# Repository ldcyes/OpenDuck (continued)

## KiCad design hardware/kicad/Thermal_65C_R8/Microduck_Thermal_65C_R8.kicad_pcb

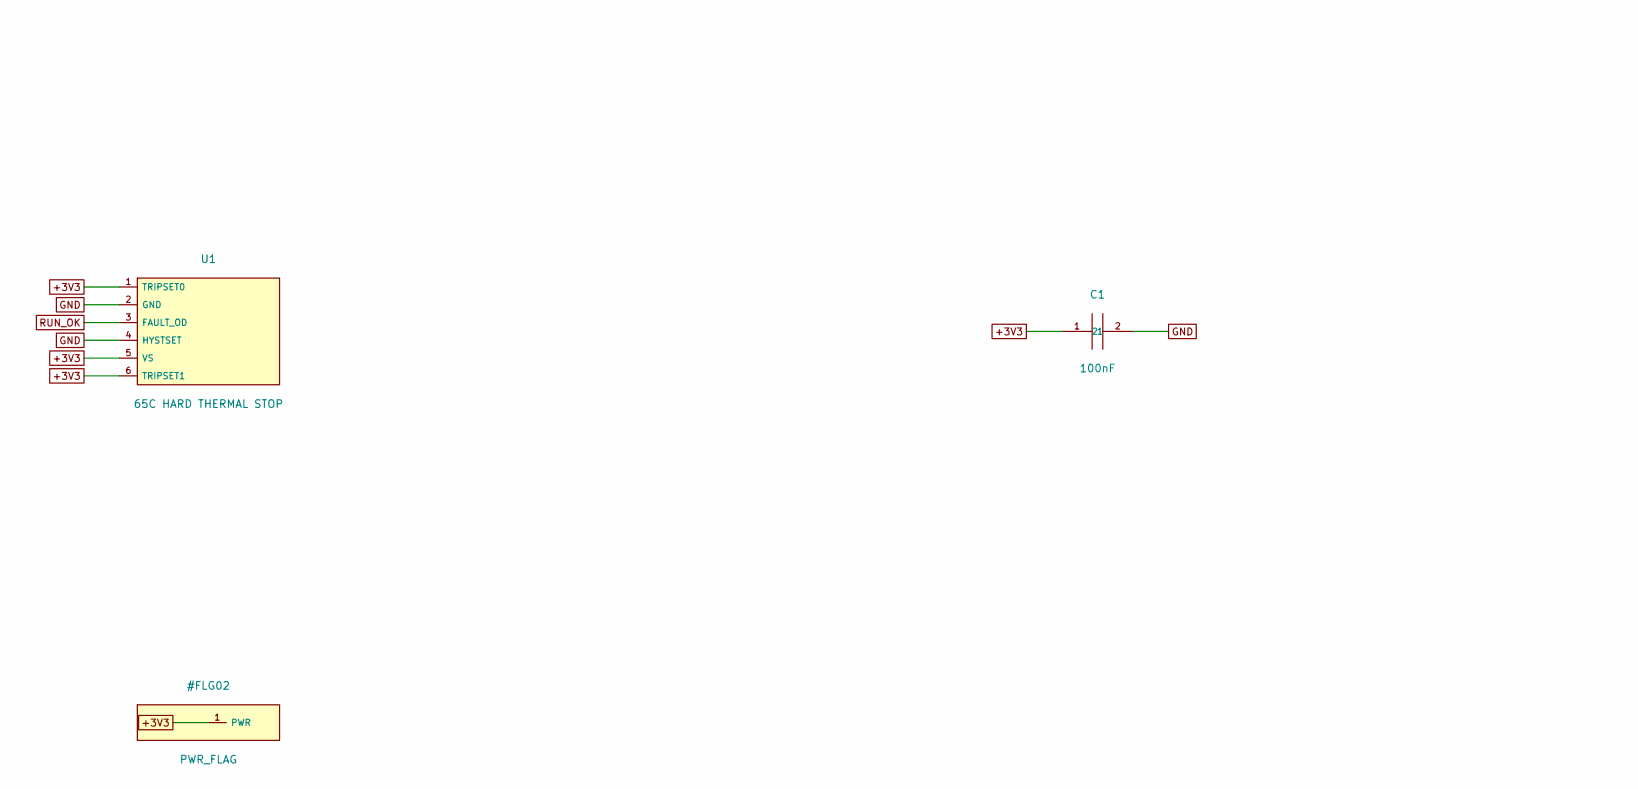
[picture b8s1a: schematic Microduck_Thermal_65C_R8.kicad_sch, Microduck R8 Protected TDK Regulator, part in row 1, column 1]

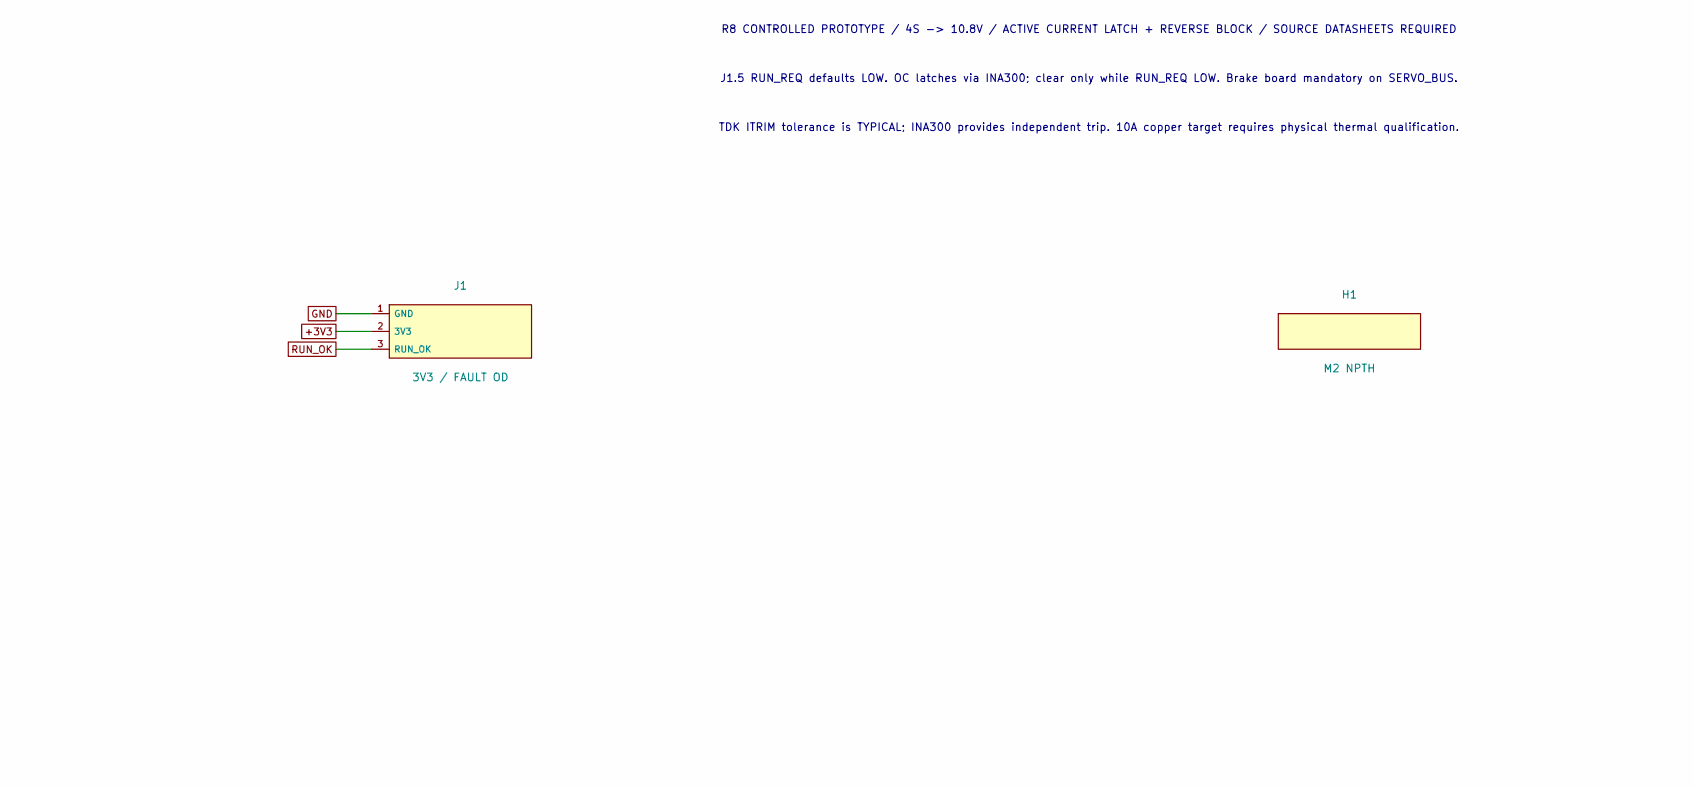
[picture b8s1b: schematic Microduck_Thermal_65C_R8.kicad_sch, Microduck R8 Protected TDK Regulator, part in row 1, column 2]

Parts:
C1: 100nF; C_0603_1608Metric; MPN GRM188R71H104KA93D
H1, H2: M2 NPTH; MountingHole_2.2mm_M2; MPN NO PART
J1: 3V3 / FAULT OD; JST_SH_SM03B-SRSS-TB_1x03-1MP_P1.00mm_Horizontal; MPN SM03B-SRSS-TB(LF)(SN)
U1: 65C HARD THERMAL STOP; SOT-563; MPN TMP302ADRLR

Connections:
+3V3: C1.1, J1.2 (3V3), U1.1 (TRIPSET0), U1.5 (VS), U1.6 (TRIPSET1)
GND: C1.2, J1.1 (GND), U1.2 (GND), U1.4 (HYSTSET)
RUN_OK: J1.3 (RUN_OK), U1.3 (FAULT_OD)

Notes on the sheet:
R8 CONTROLLED PROTOTYPE / 4S -> 10.8V / ACTIVE CURRENT LATCH + REVERSE BLOCK / SOURCE DATASHEETS REQUIRED
J1.5 RUN_REQ defaults LOW. OC latches via INA300; clear only while RUN_REQ LOW. Brake board mandatory on SERVO_BUS.
TDK ITRIM tolerance is TYPICAL; INA300 provides independent trip. 10A copper target requires physical thermal qualification.

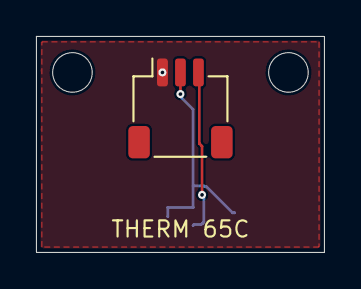
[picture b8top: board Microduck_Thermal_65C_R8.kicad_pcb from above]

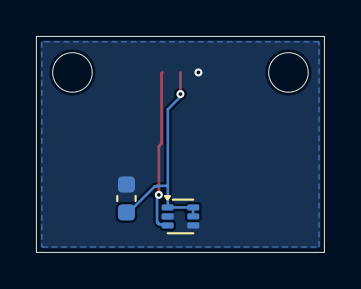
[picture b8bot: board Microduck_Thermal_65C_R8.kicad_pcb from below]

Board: 2 copper layers, 16.0 x 12.0 mm, 5 parts (2 on the bottom side), 3 nets.
